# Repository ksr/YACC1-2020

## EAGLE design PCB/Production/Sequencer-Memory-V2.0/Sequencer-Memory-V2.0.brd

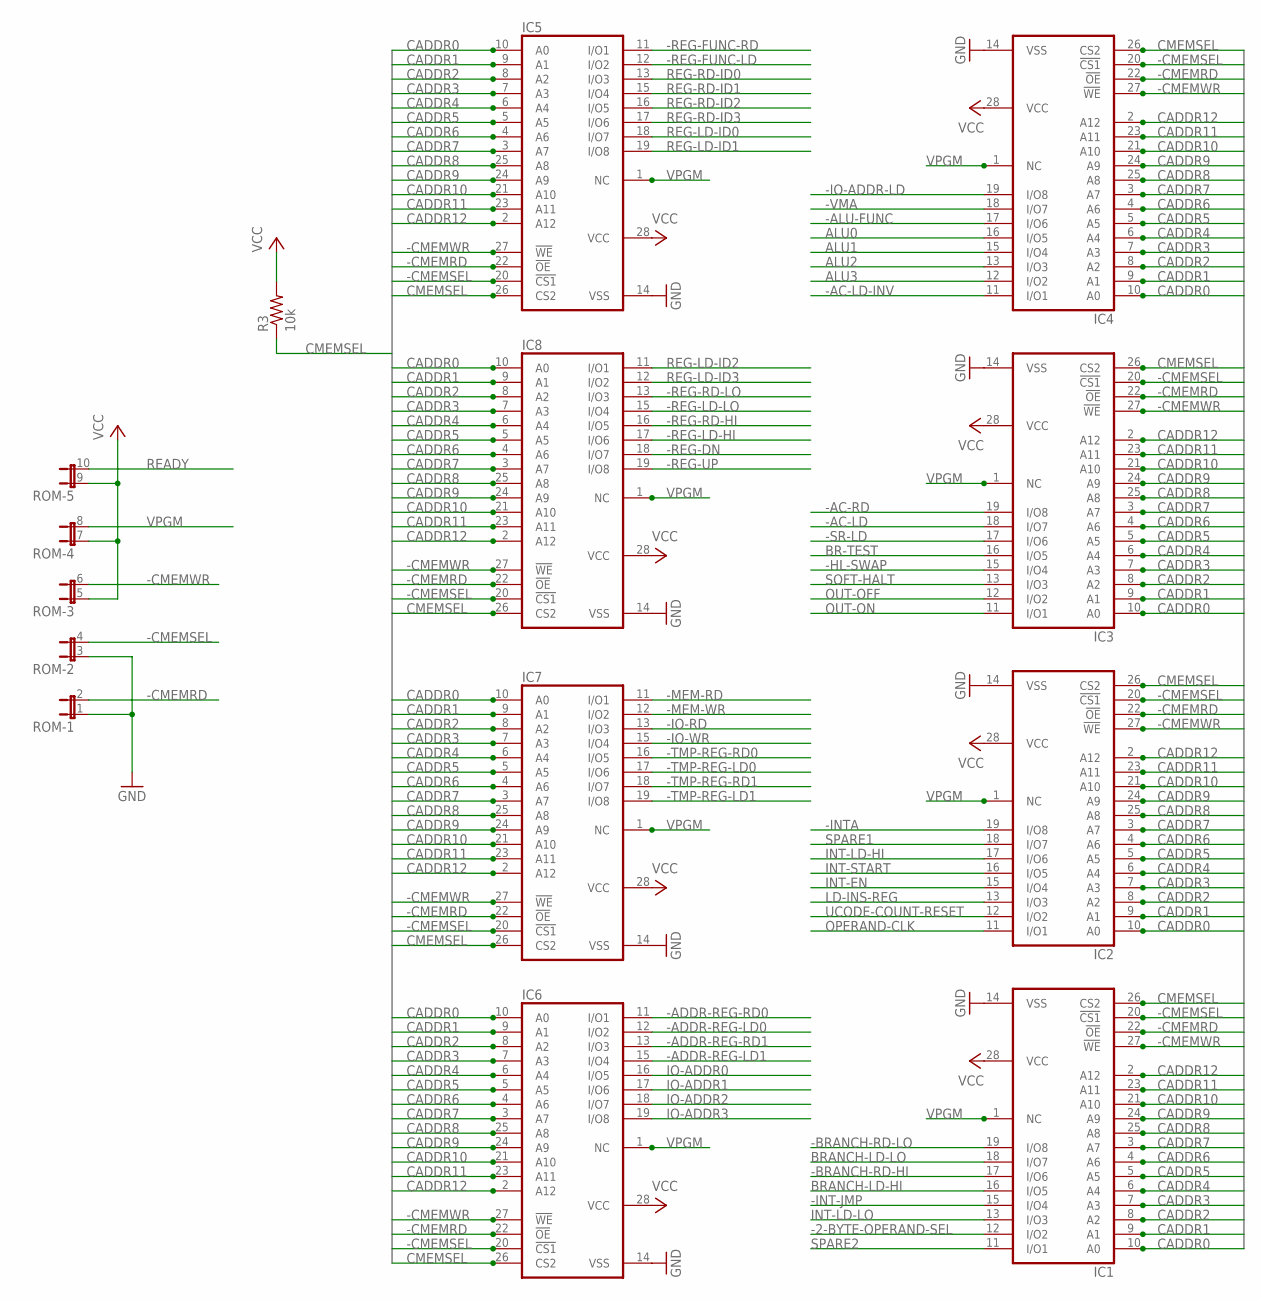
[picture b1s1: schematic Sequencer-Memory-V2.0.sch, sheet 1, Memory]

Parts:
IC1, IC2, IC3, IC4, IC5, IC6, IC7, IC8: 6264A; DIL28-6
R3: 10k; 0207/10
ROM: JP5QE; JP5Q

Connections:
-2-BYTE-OPERAND-SEL: IC1.12 (I/O2); also elsewhere on the board
-AC-LD: IC3.18 (I/O7); also elsewhere on the board
-AC-LD-INV: IC4.11 (I/O1); also elsewhere on the board
-AC-RD: IC3.19 (I/O8); also elsewhere on the board
-ADDR-REG-LD0: IC6.12 (I/O2); also elsewhere on the board
-ADDR-REG-LD1: IC6.15 (I/O4); also elsewhere on the board
-ADDR-REG-RD0: IC6.11 (I/O1); also elsewhere on the board
-ADDR-REG-RD1: IC6.13 (I/O3); also elsewhere on the board
-ALU-FUNC: IC4.17 (I/O6); also elsewhere on the board
-BRANCH-RD-HI: IC1.17 (I/O6); also elsewhere on the board
-BRANCH-RD-LO: IC1.19 (I/O8); also elsewhere on the board
-CMEMRD: IC1.22 (!OE), IC2.22 (!OE), IC3.22 (!OE), IC4.22 (!OE), IC5.22 (!OE), IC6.22 (!OE), IC7.22 (!OE), IC8.22 (!OE), ROM.2; also elsewhere on the board
-CMEMSEL: IC1.20 (!CS1), IC2.20 (!CS1), IC3.20 (!CS1), IC4.20 (!CS1), IC5.20 (!CS1), IC6.20 (!CS1), IC7.20 (!CS1), IC8.20 (!CS1), ROM.4 (2); also elsewhere on the board
-CMEMWR: IC1.27 (!WE), IC2.27 (!WE), IC3.27 (!WE), IC4.27 (!WE), IC5.27 (!WE), IC6.27 (!WE), IC7.27 (!WE), IC8.27 (!WE), ROM.6 (2); also elsewhere on the board
-HL-SWAP: IC3.15 (I/O4); also elsewhere on the board
-INT-JMP: IC1.15 (I/O4); also elsewhere on the board
-INTA: IC2.19 (I/O8); also elsewhere on the board
-IO-ADDR-LD: IC4.19 (I/O8); also elsewhere on the board
-IO-RD: IC7.13 (I/O3); also elsewhere on the board
-IO-WR: IC7.15 (I/O4); also elsewhere on the board
-MEM-RD: IC7.11 (I/O1); also elsewhere on the board
-MEM-WR: IC7.12 (I/O2); also elsewhere on the board
-REG-DN: IC8.18 (I/O7); also elsewhere on the board
-REG-FUNC-LD: IC5.12 (I/O2); also elsewhere on the board
-REG-FUNC-RD: IC5.11 (I/O1); also elsewhere on the board
-REG-LD-HI: IC8.17 (I/O6); also elsewhere on the board
-REG-LD-LO: IC8.15 (I/O4); also elsewhere on the board
-REG-RD-HI: IC8.16 (I/O5); also elsewhere on the board
-REG-RD-LO: IC8.13 (I/O3); also elsewhere on the board
-REG-UP: IC8.19 (I/O8); also elsewhere on the board
-SR-LD: IC3.17 (I/O6); also elsewhere on the board
-TMP-REG-LD0: IC7.17 (I/O6); also elsewhere on the board
-TMP-REG-LD1: IC7.19 (I/O8); also elsewhere on the board
-TMP-REG-RD0: IC7.16 (I/O5); also elsewhere on the board
-TMP-REG-RD1: IC7.18 (I/O7); also elsewhere on the board
-VMA: IC4.18 (I/O7); also elsewhere on the board
ALU0: IC4.16 (I/O5); also elsewhere on the board
ALU1: IC4.15 (I/O4); also elsewhere on the board
ALU2: IC4.13 (I/O3); also elsewhere on the board
ALU3: IC4.12 (I/O2); also elsewhere on the board
BR-TEST: IC3.16 (I/O5); also elsewhere on the board
BRANCH-LD-HI: IC1.16 (I/O5); also elsewhere on the board
BRANCH-LD-LO: IC1.18 (I/O7); also elsewhere on the board
CADDR0: IC1.10 (A0), IC2.10 (A0), IC3.10 (A0), IC4.10 (A0), IC5.10 (A0), IC6.10 (A0), IC7.10 (A0), IC8.10 (A0); also elsewhere on the board
CADDR1: IC1.9 (A1), IC2.9 (A1), IC3.9 (A1), IC4.9 (A1), IC5.9 (A1), IC6.9 (A1), IC7.9 (A1), IC8.9 (A1); also elsewhere on the board
CADDR2: IC1.8 (A2), IC2.8 (A2), IC3.8 (A2), IC4.8 (A2), IC5.8 (A2), IC6.8 (A2), IC7.8 (A2), IC8.8 (A2); also elsewhere on the board
CADDR3: IC1.7 (A3), IC2.7 (A3), IC3.7 (A3), IC4.7 (A3), IC5.7 (A3), IC6.7 (A3), IC7.7 (A3), IC8.7 (A3); also elsewhere on the board
CADDR4: IC1.6 (A4), IC2.6 (A4), IC3.6 (A4), IC4.6 (A4), IC5.6 (A4), IC6.6 (A4), IC7.6 (A4), IC8.6 (A4); also elsewhere on the board
CADDR5: IC1.5 (A5), IC2.5 (A5), IC3.5 (A5), IC4.5 (A5), IC5.5 (A5), IC6.5 (A5), IC7.5 (A5), IC8.5 (A5); also elsewhere on the board
CADDR6: IC1.4 (A6), IC2.4 (A6), IC3.4 (A6), IC4.4 (A6), IC5.4 (A6), IC6.4 (A6), IC7.4 (A6), IC8.4 (A6); also elsewhere on the board
CADDR7: IC1.3 (A7), IC2.3 (A7), IC3.3 (A7), IC4.3 (A7), IC5.3 (A7), IC6.3 (A7), IC7.3 (A7), IC8.3 (A7); also elsewhere on the board
CADDR8: IC1.25 (A8), IC2.25 (A8), IC3.25 (A8), IC4.25 (A8), IC5.25 (A8), IC6.25 (A8), IC7.25 (A8), IC8.25 (A8); also elsewhere on the board
CADDR9: IC1.24 (A9), IC2.24 (A9), IC3.24 (A9), IC4.24 (A9), IC5.24 (A9), IC6.24 (A9), IC7.24 (A9), IC8.24 (A9); also elsewhere on the board
CADDR10: IC1.21 (A10), IC2.21 (A10), IC3.21 (A10), IC4.21 (A10), IC5.21 (A10), IC6.21 (A10), IC7.21 (A10), IC8.21 (A10); also elsewhere on the board
CADDR11: IC1.23 (A11), IC2.23 (A11), IC3.23 (A11), IC4.23 (A11), IC5.23 (A11), IC6.23 (A11), IC7.23 (A11), IC8.23 (A11); also elsewhere on the board
CADDR12: IC1.2 (A12), IC2.2 (A12), IC3.2 (A12), IC4.2 (A12), IC5.2 (A12), IC6.2 (A12), IC7.2 (A12), IC8.2 (A12); also elsewhere on the board
CMEMSEL: IC1.26 (CS2), IC2.26 (CS2), IC3.26 (CS2), IC4.26 (CS2), IC5.26 (CS2), IC6.26 (CS2), IC7.26 (CS2), IC8.26 (CS2), R3.1
GND: IC1.14 (VSS), IC2.14 (VSS), IC3.14 (VSS), IC4.14 (VSS), IC5.14 (VSS), IC6.14 (VSS), IC7.14 (VSS), IC8.14 (VSS), ROM.1, ROM.3 (1); also elsewhere on the board
INT-EN: IC2.15 (I/O4); also elsewhere on the board
INT-LD-HI: IC2.17 (I/O6); also elsewhere on the board
INT-LD-LO: IC1.13 (I/O3); also elsewhere on the board
INT-START: IC2.16 (I/O5); also elsewhere on the board
IO-ADDR0: IC6.16 (I/O5); also elsewhere on the board
IO-ADDR1: IC6.17 (I/O6); also elsewhere on the board
IO-ADDR2: IC6.18 (I/O7); also elsewhere on the board
IO-ADDR3: IC6.19 (I/O8); also elsewhere on the board
LD-INS-REG: IC2.13 (I/O3); also elsewhere on the board
OPERAND-CLK: IC2.11 (I/O1); also elsewhere on the board
OUT-OFF: IC3.12 (I/O2); also elsewhere on the board
OUT-ON: IC3.11 (I/O1); also elsewhere on the board
READY: ROM.10 (2); also elsewhere on the board
REG-LD-ID0: IC5.18 (I/O7); also elsewhere on the board
REG-LD-ID1: IC5.19 (I/O8); also elsewhere on the board
REG-LD-ID2: IC8.11 (I/O1); also elsewhere on the board
REG-LD-ID3: IC8.12 (I/O2); also elsewhere on the board
REG-RD-ID0: IC5.13 (I/O3); also elsewhere on the board
REG-RD-ID1: IC5.15 (I/O4); also elsewhere on the board
REG-RD-ID2: IC5.16 (I/O5); also elsewhere on the board
REG-RD-ID3: IC5.17 (I/O6); also elsewhere on the board
SOFT-HALT: IC3.13 (I/O3); also elsewhere on the board
SPARE1: IC2.18 (I/O7); also elsewhere on the board
SPARE2: IC1.11 (I/O1); also elsewhere on the board
UCODE-COUNT-RESET: IC2.12 (I/O2); also elsewhere on the board
VCC: IC1.28 (VCC), IC2.28 (VCC), IC3.28 (VCC), IC4.28 (VCC), IC5.28 (VCC), IC6.28 (VCC), IC7.28 (VCC), IC8.28 (VCC), R3.2, ROM.5 (1), ROM.7 (1), ROM.9 (1); also elsewhere on the board
VPGM: IC1.1 (NC), IC2.1 (NC), IC3.1 (NC), IC4.1 (NC), IC5.1 (NC), IC6.1 (NC), IC7.1 (NC), IC8.1 (NC), ROM.8 (2)

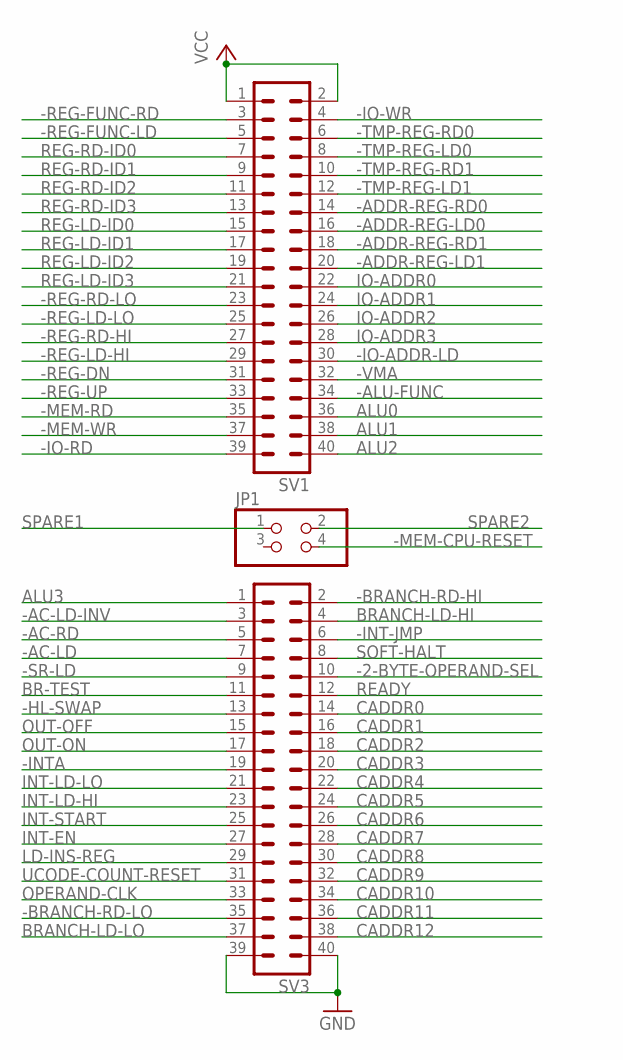
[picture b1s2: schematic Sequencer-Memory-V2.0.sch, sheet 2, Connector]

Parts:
JP1: PINHD-2X2; 2X02
SV1, SV3: MA20-2

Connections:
-2-BYTE-OPERAND-SEL: SV3.10; also elsewhere on the board
-AC-LD: SV3.7; also elsewhere on the board
-AC-LD-INV: SV3.3; also elsewhere on the board
-AC-RD: SV3.5; also elsewhere on the board
-ADDR-REG-LD0: SV1.16; also elsewhere on the board
-ADDR-REG-LD1: SV1.20; also elsewhere on the board
-ADDR-REG-RD0: SV1.14; also elsewhere on the board
-ADDR-REG-RD1: SV1.18; also elsewhere on the board
-ALU-FUNC: SV1.34; also elsewhere on the board
-BRANCH-RD-HI: SV3.2; also elsewhere on the board
-BRANCH-RD-LO: SV3.35; also elsewhere on the board
-HL-SWAP: SV3.13; also elsewhere on the board
-INT-JMP: SV3.6; also elsewhere on the board
-INTA: SV3.19; also elsewhere on the board
-IO-ADDR-LD: SV1.30; also elsewhere on the board
-IO-RD: SV1.39; also elsewhere on the board
-IO-WR: SV1.4; also elsewhere on the board
-MEM-CPU-RESET: JP1.4; also elsewhere on the board
-MEM-RD: SV1.35; also elsewhere on the board
-MEM-WR: SV1.37; also elsewhere on the board
-REG-DN: SV1.31; also elsewhere on the board
-REG-FUNC-LD: SV1.5; also elsewhere on the board
-REG-FUNC-RD: SV1.3; also elsewhere on the board
-REG-LD-HI: SV1.29; also elsewhere on the board
-REG-LD-LO: SV1.25; also elsewhere on the board
-REG-RD-HI: SV1.27; also elsewhere on the board
-REG-RD-LO: SV1.23; also elsewhere on the board
-REG-UP: SV1.33; also elsewhere on the board
-SR-LD: SV3.9; also elsewhere on the board
-TMP-REG-LD0: SV1.8; also elsewhere on the board
-TMP-REG-LD1: SV1.12; also elsewhere on the board
-TMP-REG-RD0: SV1.6; also elsewhere on the board
-TMP-REG-RD1: SV1.10; also elsewhere on the board
-VMA: SV1.32; also elsewhere on the board
ALU0: SV1.36; also elsewhere on the board
ALU1: SV1.38; also elsewhere on the board
ALU2: SV1.40; also elsewhere on the board
ALU3: SV3.1; also elsewhere on the board
BR-TEST: SV3.11; also elsewhere on the board
BRANCH-LD-HI: SV3.4; also elsewhere on the board
BRANCH-LD-LO: SV3.37; also elsewhere on the board
CADDR0: SV3.14; also elsewhere on the board
CADDR1: SV3.16; also elsewhere on the board
CADDR2: SV3.18; also elsewhere on the board
CADDR3: SV3.20; also elsewhere on the board
CADDR4: SV3.22; also elsewhere on the board
CADDR5: SV3.24; also elsewhere on the board
CADDR6: SV3.26; also elsewhere on the board
CADDR7: SV3.28; also elsewhere on the board
CADDR8: SV3.30; also elsewhere on the board
CADDR9: SV3.32; also elsewhere on the board
CADDR10: SV3.34; also elsewhere on the board
CADDR11: SV3.36; also elsewhere on the board
CADDR12: SV3.38; also elsewhere on the board
GND: SV3.39, SV3.40; also elsewhere on the board
INT-EN: SV3.27; also elsewhere on the board
INT-LD-HI: SV3.23; also elsewhere on the board
INT-LD-LO: SV3.21; also elsewhere on the board
INT-START: SV3.25; also elsewhere on the board
IO-ADDR0: SV1.22; also elsewhere on the board
IO-ADDR1: SV1.24; also elsewhere on the board
IO-ADDR2: SV1.26; also elsewhere on the board
IO-ADDR3: SV1.28; also elsewhere on the board
LD-INS-REG: SV3.29; also elsewhere on the board
OPERAND-CLK: SV3.33; also elsewhere on the board
OUT-OFF: SV3.15; also elsewhere on the board
OUT-ON: SV3.17; also elsewhere on the board
READY: SV3.12; also elsewhere on the board
REG-LD-ID0: SV1.15; also elsewhere on the board
REG-LD-ID1: SV1.17; also elsewhere on the board
REG-LD-ID2: SV1.19; also elsewhere on the board
REG-LD-ID3: SV1.21; also elsewhere on the board
REG-RD-ID0: SV1.7; also elsewhere on the board
REG-RD-ID1: SV1.9; also elsewhere on the board
REG-RD-ID2: SV1.11; also elsewhere on the board
REG-RD-ID3: SV1.13; also elsewhere on the board
SOFT-HALT: SV3.8; also elsewhere on the board
SPARE1: JP1.1; also elsewhere on the board
SPARE2: JP1.2; also elsewhere on the board
UCODE-COUNT-RESET: SV3.31; also elsewhere on the board
VCC: SV1.1, SV1.2; also elsewhere on the board

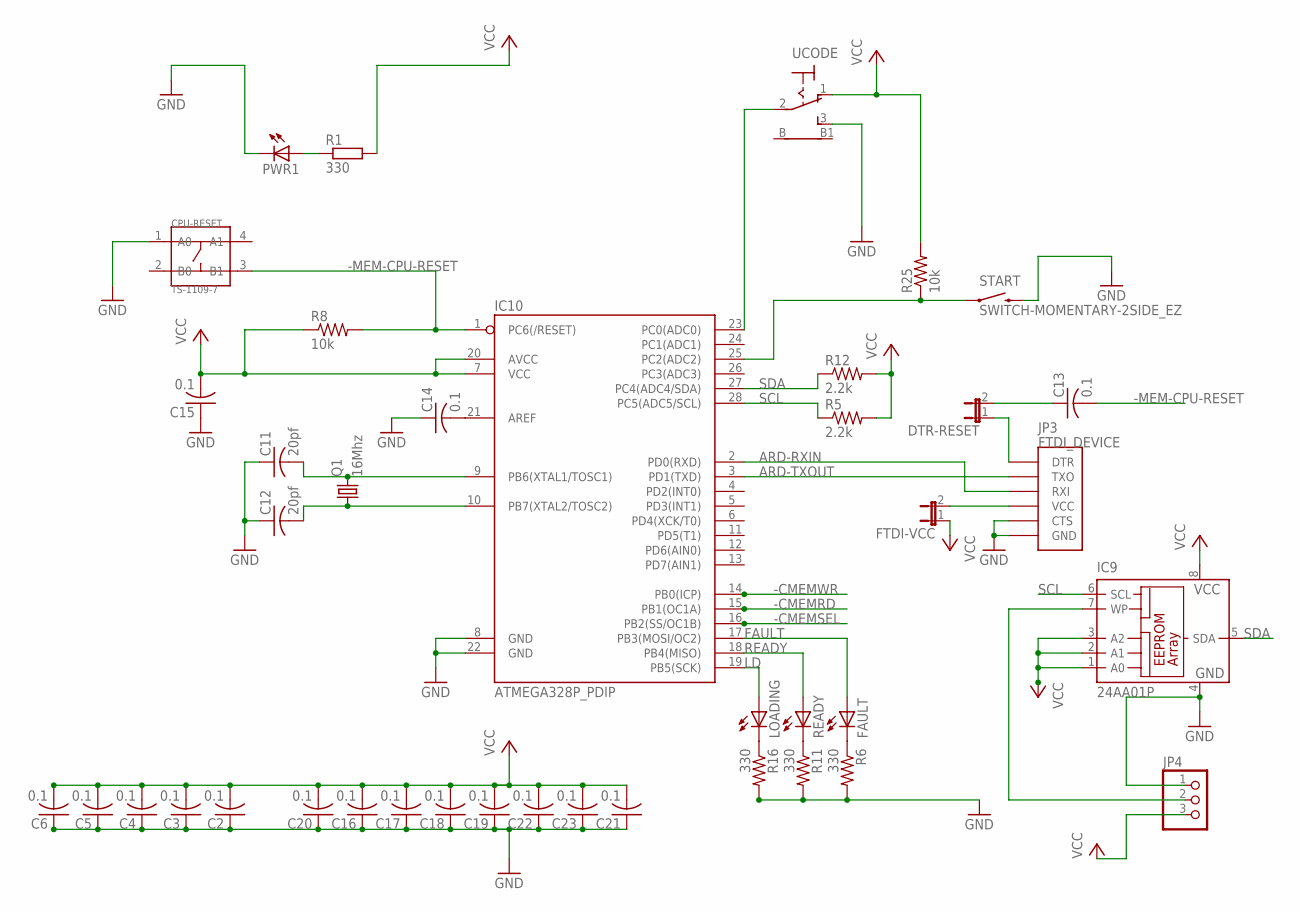
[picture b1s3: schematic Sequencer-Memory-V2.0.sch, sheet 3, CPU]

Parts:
C2, C3, C4, C5, C6, C13, C14, C15, C16, C17, C18, C19, C20, C21, C22, C23: 0.1; C025-024X044
C11, C12: 20pf; C025-024X044
CPU-RESET: TS-1109-7; SW4-6.2X6.2X5.0MM
DTR-RESET: JP1E; JP1
FAULT: LED5MM
FTDI-VCC: JP1E; JP1
IC9: 24AA01P; DIL8
IC10: ATMEGA328P_PDIP; DIL28-3
JP3: FTDI_DEVICE; FTDI_DEVICE_SIDE
JP4: PINHD-1X3; 1X03
LOADING: LED5MM
PWR1: LED5MM
Q1: 16Mhz; HC49/S
R1, R6, R11, R16: 330; 0207/10
R5, R12: 2.2k; 0207/10
R8, R25: 10k; 0207/10
READY: LED5MM
START: SWITCH-MOMENTARY-2SIDE_EZ; TACTILE-PTH-SIDEEZ
UCODE: 9070-1W

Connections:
-CMEMRD: IC10.15 (PB1(OC1A)); also elsewhere on the board
-CMEMSEL: IC10.16 (PB2(SS/OC1B)); also elsewhere on the board
-CMEMWR: IC10.14 (PB0(ICP)); also elsewhere on the board
-MEM-CPU-RESET: C13.2, CPU-RESET.3 (B1), IC10.1 (PC6(/RESET)), R8.2; also elsewhere on the board
ARD-RXIN: IC10.2 (PD0(RXD)), JP3.P$3 (RXI)
ARD-TXOUT: IC10.3 (PD1(TXD)), JP3.P$2 (TXO)
FAULT: FAULT.A, IC10.17 (PB3(MOSI/OC2))
GND: C2.1, C3.1, C4.1, C5.1, C6.1, C11.1, C12.1, C14.1, C15.1, C16.1, C17.1, C18.1, C19.1, C20.1, C21.1, C22.1, C23.1, CPU-RESET.1 (A0), IC9.4 (GND), IC10.8 (GND), IC10.22 (GND), JP3.P$5 (CTS), JP3.P$6 (GND), JP4.1, PWR1.K (C), R6.2, R11.2, R16.2, START.2, UCODE.3 (S); also elsewhere on the board
LD: IC10.19 (PB5(SCK)), LOADING.A
unnamed: PWR1.A, R1.1
unnamed: C11.2, IC10.9 (PB6(XTAL1/TOSC1)), Q1.2
unnamed: C12.2, IC10.10 (PB7(XTAL2/TOSC2)), Q1.1
unnamed: C13.1, DTR-RESET.2
unnamed: C14.2, IC10.21 (AREF)
unnamed: R11.1, READY.K (C)
unnamed: LOADING.K (C), R16.1
unnamed: FAULT.K (C), R6.1
unnamed: IC10.23 (PC0(ADC0)), UCODE.2
unnamed: IC9.7 (WP), JP4.2
unnamed: DTR-RESET.1, JP3.P$1 (DTR)
unnamed: FTDI-VCC.2, JP3.P$4 (VCC)
unnamed: IC10.25 (PC2(ADC2)), R25.1, START.1
READY: IC10.18 (PB4(MISO)), READY.A; also elsewhere on the board
SCL: IC9.6 (SCL), IC10.28 (PC5(ADC5/SCL)), R5.1; also elsewhere on the board
SDA: IC9.5 (SDA), IC10.27 (PC4(ADC4/SDA)), R12.1; also elsewhere on the board
VCC: C2.2, C3.2, C4.2, C5.2, C6.2, C15.2, C16.2, C17.2, C18.2, C19.2, C20.2, C21.2, C22.2, C23.2, FTDI-VCC.1, IC9.1 (A0), IC9.2 (A1), IC9.3 (A2), IC9.8 (VCC), IC10.7 (VCC), IC10.20 (AVCC), JP4.3, R1.2, R5.2, R8.1, R12.2, R25.2, UCODE.1 (O); also elsewhere on the board

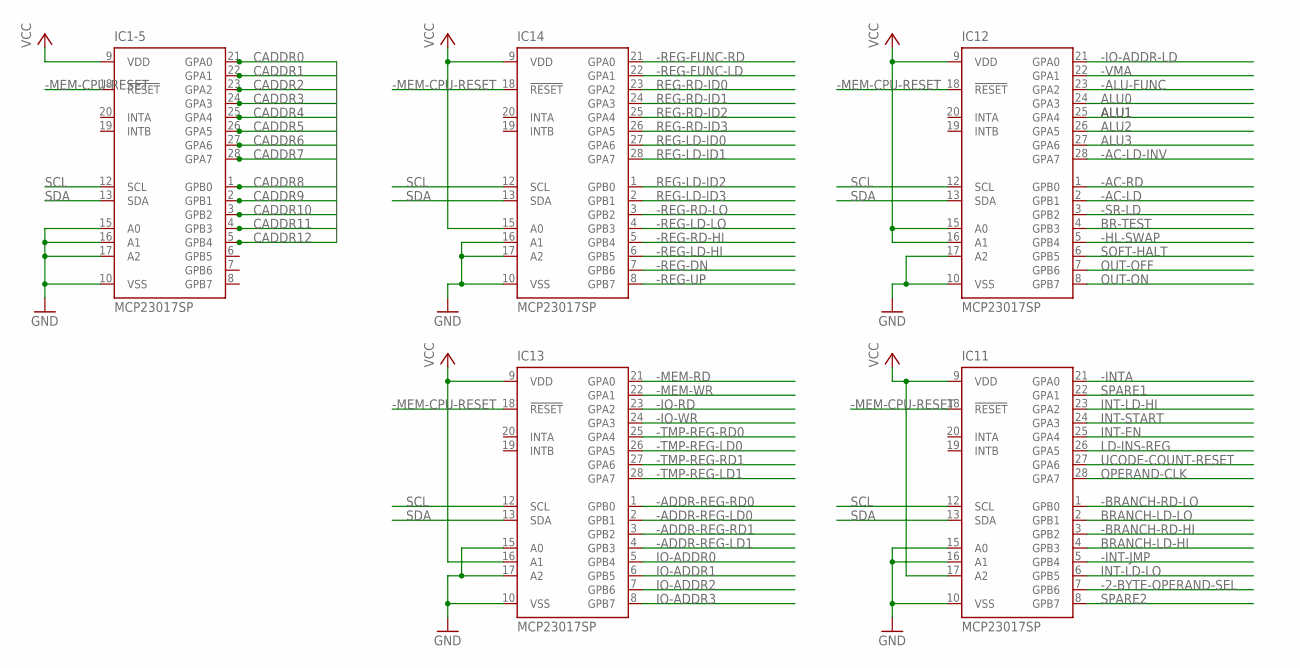
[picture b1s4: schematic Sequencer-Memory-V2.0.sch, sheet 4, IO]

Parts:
IC1-5, IC11, IC12, IC13, IC14: MCP23017SP; DIL28-3

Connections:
-2-BYTE-OPERAND-SEL: IC11.7 (GPB6); also elsewhere on the board
-AC-LD: IC12.2 (GPB1); also elsewhere on the board
-AC-LD-INV: IC12.28 (GPA7); also elsewhere on the board
-AC-RD: IC12.1 (GPB0); also elsewhere on the board
-ADDR-REG-LD0: IC13.2 (GPB1); also elsewhere on the board
-ADDR-REG-LD1: IC13.4 (GPB3); also elsewhere on the board
-ADDR-REG-RD0: IC13.1 (GPB0); also elsewhere on the board
-ADDR-REG-RD1: IC13.3 (GPB2); also elsewhere on the board
-ALU-FUNC: IC12.23 (GPA2); also elsewhere on the board
-BRANCH-RD-HI: IC11.3 (GPB2); also elsewhere on the board
-BRANCH-RD-LO: IC11.1 (GPB0); also elsewhere on the board
-HL-SWAP: IC12.5 (GPB4); also elsewhere on the board
-INT-JMP: IC11.5 (GPB4); also elsewhere on the board
-INTA: IC11.21 (GPA0); also elsewhere on the board
-IO-ADDR-LD: IC12.21 (GPA0); also elsewhere on the board
-IO-RD: IC13.23 (GPA2); also elsewhere on the board
-IO-WR: IC13.24 (GPA3); also elsewhere on the board
-MEM-CPU-RESET: IC1-5.18 (!RESET), IC11.18 (!RESET), IC12.18 (!RESET), IC13.18 (!RESET), IC14.18 (!RESET); also elsewhere on the board
-MEM-RD: IC13.21 (GPA0); also elsewhere on the board
-MEM-WR: IC13.22 (GPA1); also elsewhere on the board
-REG-DN: IC14.7 (GPB6); also elsewhere on the board
-REG-FUNC-LD: IC14.22 (GPA1); also elsewhere on the board
-REG-FUNC-RD: IC14.21 (GPA0); also elsewhere on the board
-REG-LD-HI: IC14.6 (GPB5); also elsewhere on the board
-REG-LD-LO: IC14.4 (GPB3); also elsewhere on the board
-REG-RD-HI: IC14.5 (GPB4); also elsewhere on the board
-REG-RD-LO: IC14.3 (GPB2); also elsewhere on the board
-REG-UP: IC14.8 (GPB7); also elsewhere on the board
-SR-LD: IC12.3 (GPB2); also elsewhere on the board
-TMP-REG-LD0: IC13.26 (GPA5); also elsewhere on the board
-TMP-REG-LD1: IC13.28 (GPA7); also elsewhere on the board
-TMP-REG-RD0: IC13.25 (GPA4); also elsewhere on the board
-TMP-REG-RD1: IC13.27 (GPA6); also elsewhere on the board
-VMA: IC12.22 (GPA1); also elsewhere on the board
ALU0: IC12.24 (GPA3); also elsewhere on the board
ALU1: IC12.25 (GPA4); also elsewhere on the board
ALU2: IC12.26 (GPA5); also elsewhere on the board
ALU3: IC12.27 (GPA6); also elsewhere on the board
BR-TEST: IC12.4 (GPB3); also elsewhere on the board
BRANCH-LD-HI: IC11.4 (GPB3); also elsewhere on the board
BRANCH-LD-LO: IC11.2 (GPB1); also elsewhere on the board
CADDR0: IC1-5.21 (GPA0); also elsewhere on the board
CADDR1: IC1-5.22 (GPA1); also elsewhere on the board
CADDR2: IC1-5.23 (GPA2); also elsewhere on the board
CADDR3: IC1-5.24 (GPA3); also elsewhere on the board
CADDR4: IC1-5.25 (GPA4); also elsewhere on the board
CADDR5: IC1-5.26 (GPA5); also elsewhere on the board
CADDR6: IC1-5.27 (GPA6); also elsewhere on the board
CADDR7: IC1-5.28 (GPA7); also elsewhere on the board
CADDR8: IC1-5.1 (GPB0); also elsewhere on the board
CADDR9: IC1-5.2 (GPB1); also elsewhere on the board
CADDR10: IC1-5.3 (GPB2); also elsewhere on the board
CADDR11: IC1-5.4 (GPB3); also elsewhere on the board
CADDR12: IC1-5.5 (GPB4); also elsewhere on the board
GND: IC1-5.10 (VSS), IC1-5.15 (A0), IC1-5.16 (A1), IC1-5.17 (A2), IC11.10 (VSS), IC11.15 (A0), IC11.16 (A1), IC12.10 (VSS), IC12.17 (A2), IC13.10 (VSS), IC13.15 (A0), IC13.17 (A2), IC14.10 (VSS), IC14.16 (A1), IC14.17 (A2); also elsewhere on the board
INT-EN: IC11.25 (GPA4); also elsewhere on the board
INT-LD-HI: IC11.23 (GPA2); also elsewhere on the board
INT-LD-LO: IC11.6 (GPB5); also elsewhere on the board
INT-START: IC11.24 (GPA3); also elsewhere on the board
IO-ADDR0: IC13.5 (GPB4); also elsewhere on the board
IO-ADDR1: IC13.6 (GPB5); also elsewhere on the board
IO-ADDR2: IC13.7 (GPB6); also elsewhere on the board
IO-ADDR3: IC13.8 (GPB7); also elsewhere on the board
LD-INS-REG: IC11.26 (GPA5); also elsewhere on the board
OPERAND-CLK: IC11.28 (GPA7); also elsewhere on the board
OUT-OFF: IC12.7 (GPB6); also elsewhere on the board
OUT-ON: IC12.8 (GPB7); also elsewhere on the board
REG-LD-ID0: IC14.27 (GPA6); also elsewhere on the board
REG-LD-ID1: IC14.28 (GPA7); also elsewhere on the board
REG-LD-ID2: IC14.1 (GPB0); also elsewhere on the board
REG-LD-ID3: IC14.2 (GPB1); also elsewhere on the board
REG-RD-ID0: IC14.23 (GPA2); also elsewhere on the board
REG-RD-ID1: IC14.24 (GPA3); also elsewhere on the board
REG-RD-ID2: IC14.25 (GPA4); also elsewhere on the board
REG-RD-ID3: IC14.26 (GPA5); also elsewhere on the board
SCL: IC1-5.12 (SCL), IC11.12 (SCL), IC12.12 (SCL), IC13.12 (SCL), IC14.12 (SCL); also elsewhere on the board
SDA: IC1-5.13 (SDA), IC11.13 (SDA), IC12.13 (SDA), IC13.13 (SDA), IC14.13 (SDA); also elsewhere on the board
SOFT-HALT: IC12.6 (GPB5); also elsewhere on the board
SPARE1: IC11.22 (GPA1); also elsewhere on the board
SPARE2: IC11.8 (GPB7); also elsewhere on the board
UCODE-COUNT-RESET: IC11.27 (GPA6); also elsewhere on the board
VCC: IC1-5.9 (VDD), IC11.9 (VDD), IC11.17 (A2), IC12.9 (VDD), IC12.15 (A0), IC12.16 (A1), IC13.9 (VDD), IC13.16 (A1), IC14.9 (VDD), IC14.15 (A0); also elsewhere on the board

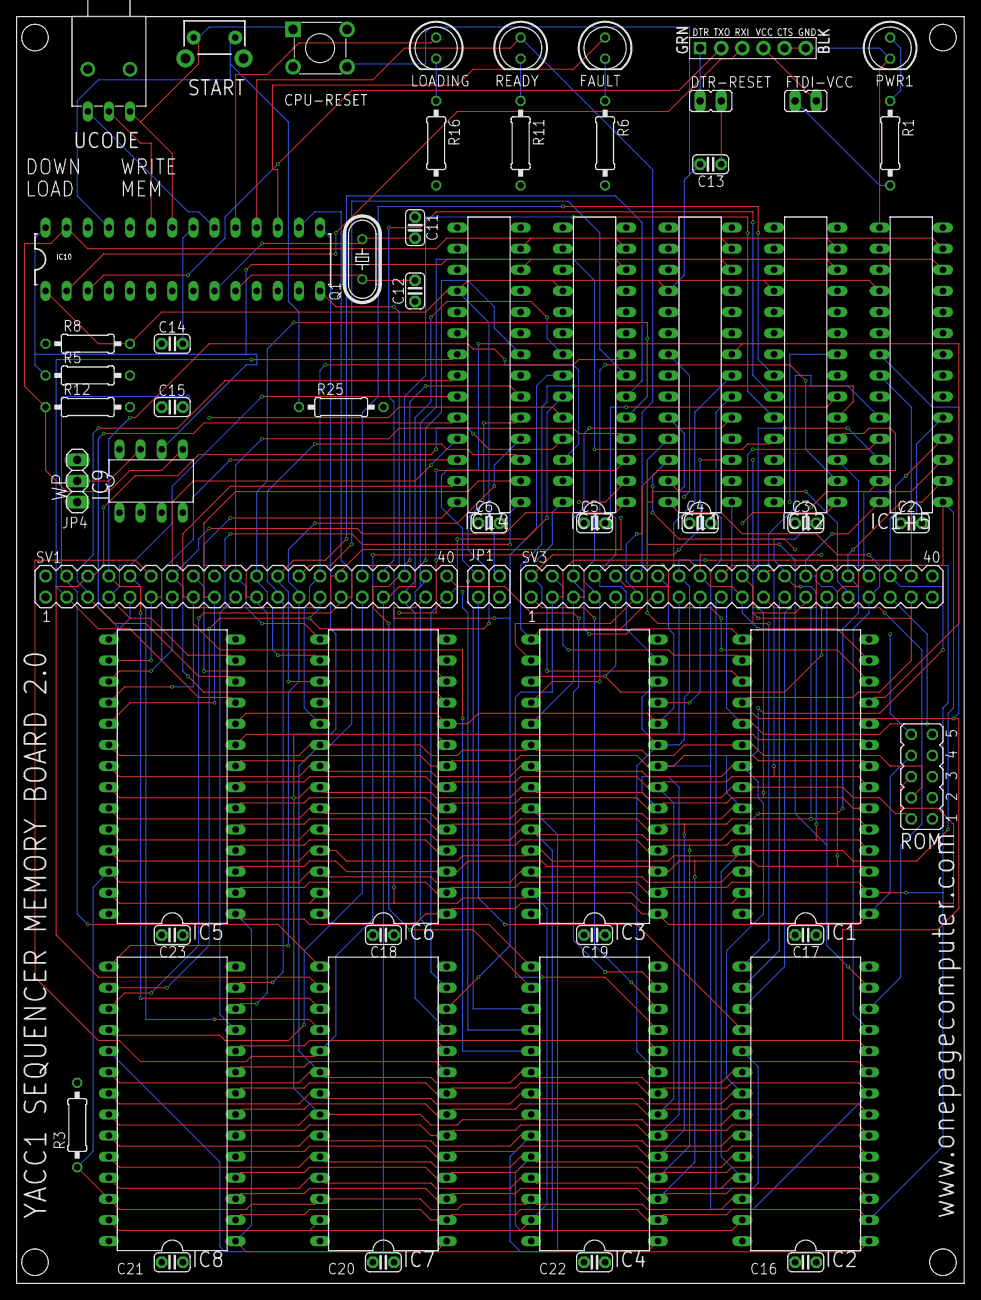
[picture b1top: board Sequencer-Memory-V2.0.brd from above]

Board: 4 copper layers, 114.0 x 152.4 mm, 58 parts (0 on the bottom side), 105 nets.

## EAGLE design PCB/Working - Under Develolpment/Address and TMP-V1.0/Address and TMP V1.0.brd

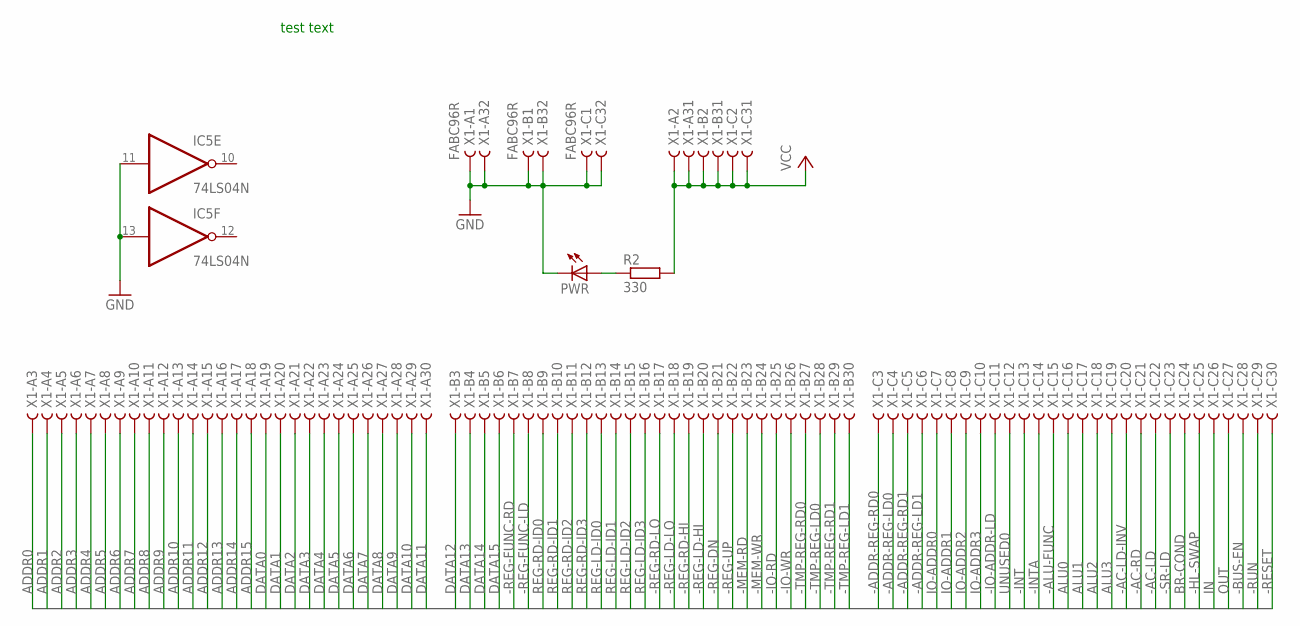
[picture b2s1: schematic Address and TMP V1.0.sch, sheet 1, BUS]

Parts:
IC5: 74LS04N; DIL14
PWR: LED5MM
R2: 330; 0207/10
X1: FABC96R

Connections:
-AC-LD: X1.C22
-AC-LD-INV: X1.C20
-AC-RD: X1.C21
-ADDR-REG-LD0: X1.C4; also elsewhere on the board
-ADDR-REG-LD1: X1.C6; also elsewhere on the board
-ADDR-REG-RD0: X1.C3; also elsewhere on the board
-ADDR-REG-RD1: X1.C5; also elsewhere on the board
-ALU-FUNC: X1.C15
-BUS-EN: X1.C28
-HL-SWAP: X1.C25
-INT: X1.C13
-INTA: X1.C14
-IO-ADDR-LD: X1.C11
-IO-RD: X1.B25
-IO-WR: X1.B26
-MEM-RD: X1.B23
-MEM-WR: X1.B24
-REG-DN: X1.B21
-REG-FUNC-LD: X1.B8
-REG-FUNC-RD: X1.B7
-REG-LD-HI: X1.B20
-REG-LD-LO: X1.B18
-REG-RD-HI: X1.B19
-REG-RD-LO: X1.B17
-REG-UP: X1.B22
-RESET: X1.C30
-RUN: X1.C29
-SR-LD: X1.C23
-TMP-REG-LD0: X1.B28; also elsewhere on the board
-TMP-REG-LD1: X1.B30; also elsewhere on the board
-TMP-REG-RD0: X1.B27; also elsewhere on the board
-TMP-REG-RD1: X1.B29; also elsewhere on the board
ADDR0: X1.A3; also elsewhere on the board
ADDR1: X1.A4; also elsewhere on the board
ADDR2: X1.A5; also elsewhere on the board
ADDR3: X1.A6; also elsewhere on the board
ADDR4: X1.A7; also elsewhere on the board
ADDR5: X1.A8; also elsewhere on the board
ADDR6: X1.A9; also elsewhere on the board
ADDR7: X1.A10; also elsewhere on the board
ADDR8: X1.A11; also elsewhere on the board
ADDR9: X1.A12; also elsewhere on the board
ADDR10: X1.A13; also elsewhere on the board
ADDR11: X1.A14; also elsewhere on the board
ADDR12: X1.A15; also elsewhere on the board
ADDR13: X1.A16; also elsewhere on the board
ADDR14: X1.A17; also elsewhere on the board
ADDR15: X1.A18; also elsewhere on the board
ALU0: X1.C16
ALU1: X1.C17
ALU2: X1.C18
ALU3: X1.C19
BR-COND: X1.C24
DATA0: X1.A19; also elsewhere on the board
DATA1: X1.A20; also elsewhere on the board
DATA2: X1.A21; also elsewhere on the board
DATA3: X1.A22; also elsewhere on the board
DATA4: X1.A23; also elsewhere on the board
DATA5: X1.A24; also elsewhere on the board
DATA6: X1.A25; also elsewhere on the board
DATA7: X1.A26; also elsewhere on the board
DATA8: X1.A27; also elsewhere on the board
DATA9: X1.A28; also elsewhere on the board
DATA10: X1.A29; also elsewhere on the board
DATA11: X1.A30; also elsewhere on the board
DATA12: X1.B3; also elsewhere on the board
DATA13: X1.B4; also elsewhere on the board
DATA14: X1.B5; also elsewhere on the board
DATA15: X1.B6; also elsewhere on the board
GND: IC5.7 (GND), IC5.11 (I), IC5.13 (I), PWR.K (C), X1.A1, X1.A32, X1.B1, X1.B32, X1.C1, X1.C32; also elsewhere on the board
IN: X1.C26
IO-ADDR0: X1.C7
IO-ADDR1: X1.C8
IO-ADDR2: X1.C9
IO-ADDR3: X1.C10
unnamed: PWR.A, R2.1
OUT: X1.C27
REG-LD-ID0: X1.B13
REG-LD-ID1: X1.B14
REG-LD-ID2: X1.B15
REG-LD-ID3: X1.B16
REG-RD-ID0: X1.B9
REG-RD-ID1: X1.B10
REG-RD-ID2: X1.B11
REG-RD-ID3: X1.B12
UNUSED0: X1.C12
VCC: IC5.14 (VCC), R2.2, X1.A2, X1.A31, X1.B2, X1.B31, X1.C2, X1.C31; also elsewhere on the board

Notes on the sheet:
test text

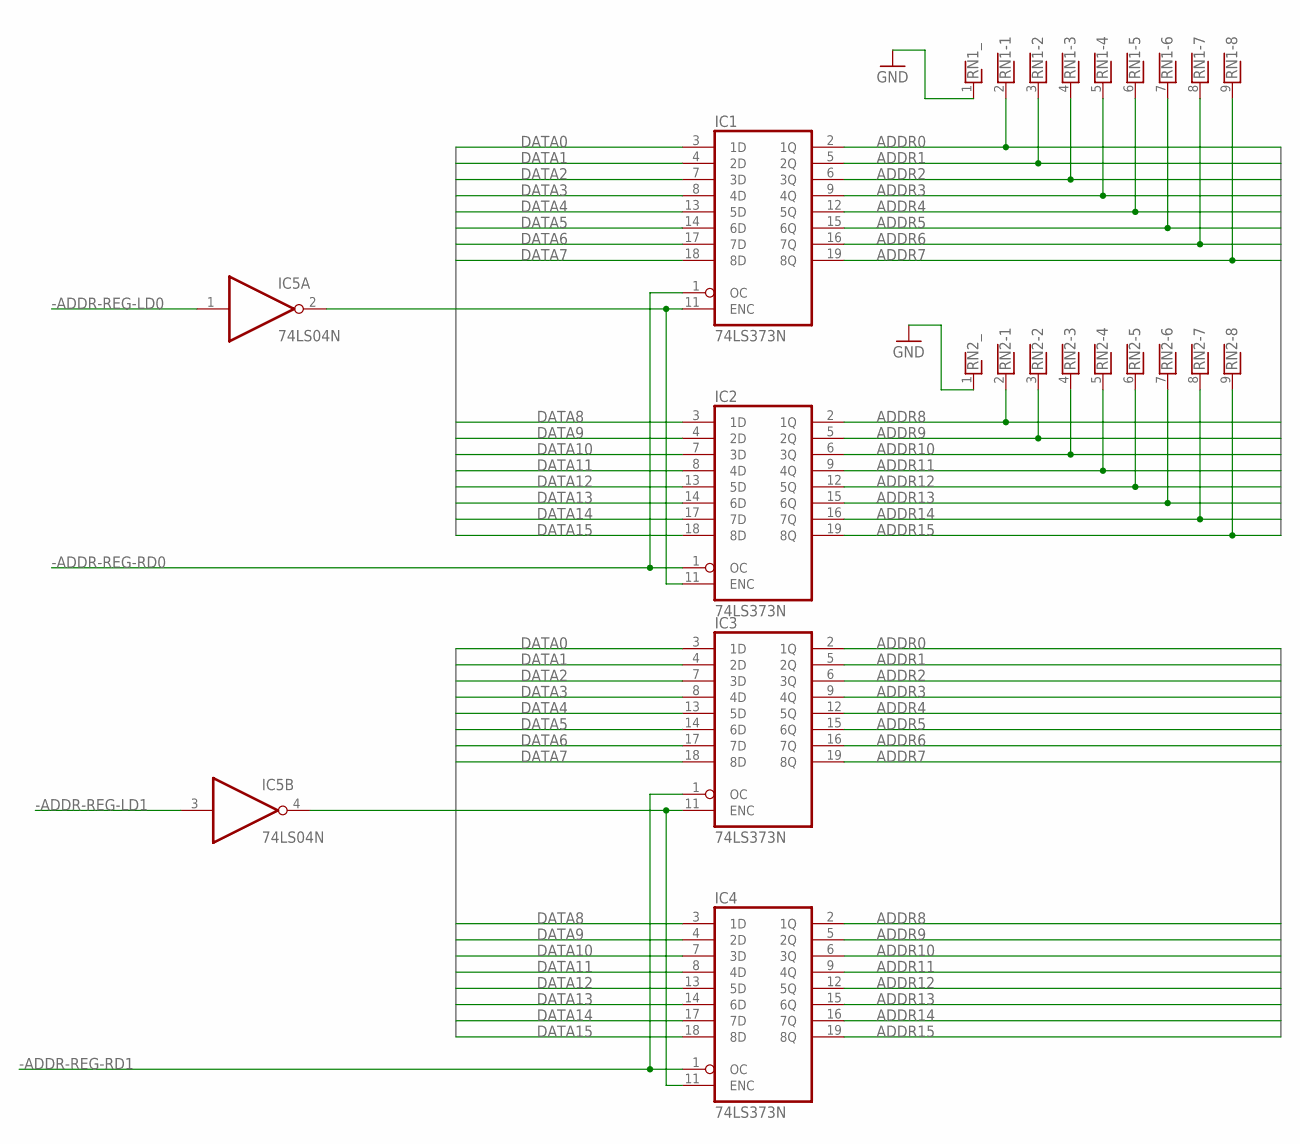
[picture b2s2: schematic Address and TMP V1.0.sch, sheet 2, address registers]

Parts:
IC1, IC2, IC3, IC4: 74LS373N; DIL20
IC5: 74LS04N; DIL14
RN1, RN2: RNX8; RN-9

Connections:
-ADDR-REG-LD0: IC5.1 (I); also elsewhere on the board
-ADDR-REG-LD1: IC5.3 (I); also elsewhere on the board
-ADDR-REG-RD0: IC1.1 (OC), IC2.1 (OC); also elsewhere on the board
-ADDR-REG-RD1: IC3.1 (OC), IC4.1 (OC); also elsewhere on the board
ADDR0: IC1.2 (1Q), IC3.2 (1Q), RN1.2; also elsewhere on the board
ADDR1: IC1.5 (2Q), IC3.5 (2Q), RN1.3; also elsewhere on the board
ADDR2: IC1.6 (3Q), IC3.6 (3Q), RN1.4; also elsewhere on the board
ADDR3: IC1.9 (4Q), IC3.9 (4Q), RN1.5; also elsewhere on the board
ADDR4: IC1.12 (5Q), IC3.12 (5Q), RN1.6; also elsewhere on the board
ADDR5: IC1.15 (6Q), IC3.15 (6Q), RN1.7; also elsewhere on the board
ADDR6: IC1.16 (7Q), IC3.16 (7Q), RN1.8; also elsewhere on the board
ADDR7: IC1.19 (8Q), IC3.19 (8Q), RN1.9; also elsewhere on the board
ADDR8: IC2.2 (1Q), IC4.2 (1Q), RN2.2; also elsewhere on the board
ADDR9: IC2.5 (2Q), IC4.5 (2Q), RN2.3; also elsewhere on the board
ADDR10: IC2.6 (3Q), IC4.6 (3Q), RN2.4; also elsewhere on the board
ADDR11: IC2.9 (4Q), IC4.9 (4Q), RN2.5; also elsewhere on the board
ADDR12: IC2.12 (5Q), IC4.12 (5Q), RN2.6; also elsewhere on the board
ADDR13: IC2.15 (6Q), IC4.15 (6Q), RN2.7; also elsewhere on the board
ADDR14: IC2.16 (7Q), IC4.16 (7Q), RN2.8; also elsewhere on the board
ADDR15: IC2.19 (8Q), IC4.19 (8Q), RN2.9; also elsewhere on the board
DATA0: IC1.3 (1D), IC3.3 (1D); also elsewhere on the board
DATA1: IC1.4 (2D), IC3.4 (2D); also elsewhere on the board
DATA2: IC1.7 (3D), IC3.7 (3D); also elsewhere on the board
DATA3: IC1.8 (4D), IC3.8 (4D); also elsewhere on the board
DATA4: IC1.13 (5D), IC3.13 (5D); also elsewhere on the board
DATA5: IC1.14 (6D), IC3.14 (6D); also elsewhere on the board
DATA6: IC1.17 (7D), IC3.17 (7D); also elsewhere on the board
DATA7: IC1.18 (8D), IC3.18 (8D); also elsewhere on the board
DATA8: IC2.3 (1D), IC4.3 (1D); also elsewhere on the board
DATA9: IC2.4 (2D), IC4.4 (2D); also elsewhere on the board
DATA10: IC2.7 (3D), IC4.7 (3D); also elsewhere on the board
DATA11: IC2.8 (4D), IC4.8 (4D); also elsewhere on the board
DATA12: IC2.13 (5D), IC4.13 (5D); also elsewhere on the board
DATA13: IC2.14 (6D), IC4.14 (6D); also elsewhere on the board
DATA14: IC2.17 (7D), IC4.17 (7D); also elsewhere on the board
DATA15: IC2.18 (8D), IC4.18 (8D); also elsewhere on the board
GND: IC1.10 (GND), IC2.10 (GND), IC3.10 (GND), IC4.10 (GND), IC5.7 (GND), RN1.1, RN2.1; also elsewhere on the board
unnamed: IC1.11 (ENC), IC2.11 (ENC), IC5.2 (O)
unnamed: IC3.11 (ENC), IC4.11 (ENC), IC5.4 (O)
VCC: IC1.20 (VCC), IC2.20 (VCC), IC3.20 (VCC), IC4.20 (VCC), IC5.14 (VCC); also elsewhere on the board

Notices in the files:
parts and their libraries:
SparkFun-Aesthetics: Licensing: Creative Commons ShareAlike 4.0 International - https://creativecommons.org/licenses/by-sa/4.0
SparkFun-DigitalIC: Licensing: CC v3.0 Share-Alike You are welcome to use this library for commercial purposes.
